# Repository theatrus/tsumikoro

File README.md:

# Tsumikoro

Open-source motor controller projects based on STM32G0 microcontrollers with ESP32 network bridge.

## Projects

| Project | Description | MCU | Flash/RAM | Framework | Status |
|---------|-------------|-----|-----------|-----------|--------|
| **tsumikoro-servo** | 6-channel servo + H-bridge motor controller | STM32G030F6P6TR | 32KB/8KB | STM32 LL | ✅ Functional (PR #9) |
| **tsumikoro-ministepper** | Mini stepper motor controller | STM32G071G8U6 | 64KB/36KB | STM32 HAL + FreeRTOS | 🚧 In Development |
| **tsumikoro-bridge** | WiFi/Network bridge (RS-485 bus) | ESP32/ESP32-S3 | 4MB+ | ESPHome | ✅ Functional (Merged) |
| **nucleo-g071rb** | Development firmware (bare-metal) | STM32G071RBT6 | 128KB/36KB | STM32 HAL | ✅ Development Tool (PR #11) |
| **nucleo-g071rb-freertos** | Development firmware (FreeRTOS) | STM32G071RBT6 | 128KB/36KB | STM32 HAL + FreeRTOS | ✅ Development Tool (PR #11) |

### Recent Updates

- **2025-11**: NUCLEO-G071RB development firmware with FreeRTOS integration (PR #11)
  - Bare-metal and FreeRTOS examples for bus protocol development
  - Stack monitoring and optimization (18KB heap, optimized task stacks)
  - Debug UART with statistics output and stack high-water marks
  - CI/CD integration for all firmware targets
- **2025-11**: Protocol improvements and bug fixes
  - Fixed escape sequence handling in packet END marker detection
  - Added comprehensive unit tests for bus handler (34 tests)
  - Integration tests for controller/peripheral communication
- **2025-11**: Multi-drop RS-485 bus protocol implemented with STM32 HAL
- **2025-11**: Servo controller: 6 PWM channels + H-bridge motor driver (89% Flash usage)
- **2025-11**: ESP32 bridge with Home Assistant integration
- **2025-11**: Unified build system with top-level Makefile and flash targets

## Repository Structure

```
tsumikoro/
├── firmware/                 # All firmware projects (C/C++, Apache 2.0)
│   ├── tsumikoro-ministepper/  # STM32G071 mini stepper controller (FreeRTOS)
│   ├── tsumikoro-servo/        # STM32G030 servo controller (bare-metal)
│   ├── tsumikoro-bridge/       # ESP32/ESP32-S3 network bridge (ESPHome)
│   │   ├── esphome/           # ESPHome configuration
│   │   └── components/        # Custom ESPHome components
│   ├── nucleo-g071rb/         # NUCLEO-G071RB development firmware (bare-metal)
│   ├── nucleo-g071rb-freertos/# NUCLEO-G071RB development firmware (FreeRTOS)
│   ├── common/                # Shared HAL and utilities (STM32, FreeRTOS)
│   └── shared/                # Shared protocol definitions and tests
│       └── tsumikoro_bus/    # Bus protocol library with unit tests
├── hardware/                 # PCB designs (coming soon, CERN-OHL-P v2)
├── mechanical/               # 3D models (coming soon, CERN-OHL-P v2)
└── LICENSE                  # Dual licensing information
```

## Quick Start

### Prerequisites

**For STM32 builds:**
- ARM GCC toolchain: `arm-none-eabi-gcc`
- CMake 3.20 or newer
- Make or Ninja build tool

**For ESP32 bridge:**
- Python 3.10+
- uv (Python package manager)

See [firmware/README.md](firmware/README.md) for detailed installation instructions.

### Build All Projects

```bash
# First-time setup
make setup

# Build everything
make build

# Or build individual projects
make build-servo       # STM32G030 servo controller
make build-ministepper # STM32G071 stepper controller
make build-bridge      # ESP32 network bridge
make build-nucleo      # NUCLEO-G071RB development boards

# Run protocol tests
make test

# Clean all builds
make clean

# View all available targets
make help
```

### Individual Project Builds

**Servo Controller (STM32G030):**
```bash
cd firmware
make servo-g030
make flash-servo-g030  # Flash using st-flash
# Output: build/servo-g030/tsumikoro-servo.bin
```

**Ministepper (STM32G071):**
```bash
cd firmware
make ministepper-g071
make flash-ministepper-g071
# Output: build/ministepper-g071/tsumikoro-ministepper.bin
```

**NUCLEO-G071RB Development Boards:**
```bash
cd firmware

# Bare-metal version
make nucleo-g071rb
make flash-nucleo-g071rb

# FreeRTOS version (with stack monitoring)
make nucleo-g071rb-freertos
make flash-nucleo-g071rb-freertos

# Reset target after flashing
make reset
```

**ESP32 Bridge:**
```bash
# First time setup
cd firmware/tsumikoro-bridge
make setup
cp esphome/secrets.yaml.example esphome/secrets.yaml
# Edit secrets.yaml with your WiFi credentials

# Build and upload
make build
make upload
```

## Key Features

### Tsumikoro Bus Protocol

Multi-drop RS-485 serial bus protocol for reliable motor controller communication:

- **Frame Format**: `[START][ID][CMD_HI][CMD_LO][LEN][DATA][CRC8][END]`
- **Packet Size**: 7-71 bytes (0-64 bytes data payload)
- **Addressing**: Controller (0x00) + up to 239 peripherals (0x01-0xEF)
- **Error Detection**: CRC8 checksum with frame markers
- **Command Ranges**:
  - `0x0000-0x0FFF`: Generic commands (ping, version, status)
  - `0x2000-0x2FFF`: Stepper motor commands
  - `0x3000-0x3FFF`: Servo motor commands
  - `0x4000-0x4FFF`: DC motor/H-bridge commands

### Servo Controller Features

**Hardware Capabilities:**
- 6 independent servo channels (50Hz PWM, 1-2ms pulse width)
- H-bridge motor driver (20kHz PWM speed control)
- 4 direction modes: FORWARD, REVERSE, BRAKE, COAST
- 0-180° servo position range (0.1° resolution)

**Control Features:**
- Smooth position transitions with configurable speed
- Per-channel calibration (500-2500µs pulse widths)
- Multi-servo synchronized movement
- Emergency stop function
- Hardware ID pins for device enumeration

**Resource Efficient:**
- Flash: 29.3KB / 32KB (89.42%)
- RAM: 2.2KB / 8KB (26.86%)
- Zero CPU overhead for PWM (hardware timers)

### ESP32 Bridge Features

- WiFi 802.11 b/g/n connectivity
- Home Assistant integration via ESPHome
- RS-485 bus communication with motor controllers
- Custom ESPHome components for Tsumikoro protocol
- OTA firmware updates

### FreeRTOS Integration

**Real-Time Operating System Support:**
- Preemptive multitasking with configurable priorities
- Dedicated RTOS threads for RX, TX, and bus handler
- Inter-task communication via queues and semaphores
- Stack overflow detection and monitoring
- Optimized heap and stack allocations (18KB heap, task-specific stacks)

**Development Tools:**
- Stack high-water mark monitoring via debug UART
- Runtime statistics (heap usage, IRQ counts, task states)
- Comprehensive unit tests for protocol and bus handler
- CI/CD integration for automated builds and testing

### Continuous Integration

**Automated Builds:**
- All firmware targets built automatically on push/PR
- Protocol unit tests run on every commit
- Artifacts retained for 30 days
- Multi-platform support (STM32 + ESP32)

**Build Matrix:**
- STM32 builds: servo-g030, ministepper-g071, nucleo-g071rb, nucleo-g071rb-freertos
- ESP32 builds: tsumikoro-bridge (ESPHome)
- Protocol tests: 151 assertions across CRC8, protocol, integration, and bus handler tests

## Hardware

### Motor Controllers (STM32)

**STM32G071G8U6** (Mini Stepper)
- 64KB Flash, 36KB RAM
- ARM Cortex-M0+ @ 64MHz
- UFQFPN28 package
- FreeRTOS support with optimized task stacks

**STM32G030F6P6TR** (Servo)
- 32KB Flash, 8KB RAM
- ARM Cortex-M0+ @ 64MHz
- TSSOP20 package
- Bare-metal for maximum efficiency

### Development Boards

**STM32 NUCLEO-G071RB**
- 128KB Flash, 36KB RAM
- ARM Cortex-M0+ @ 64MHz
- Arduino-compatible headers
- On-board ST-LINK debugger
- Available in both bare-metal and FreeRTOS firmware variants
- Ideal for bus protocol development and testing

### Network Bridge (ESP32)

**ESP32 / ESP32-S3**
- WiFi 802.11 b/g/n
- 4MB+ Flash recommended
- UART communication with motor controllers
- Home Assistant integration via ESPHome

## License

This project uses dual licensing:

- **Firmware/Software**: [Apache 2.0](firmware/LICENSE)
- **Hardware Designs**: CERN-OHL-P v2 (permissive open hardware)

See [LICENSE](LICENSE) for details.

## Contributing

Contributions are welcome! Please ensure:
- Firmware contributions follow the Apache 2.0 license
- Hardware contributions follow CERN-OHL-P v2
- Code follows the existing style
- All changes are tested

## Resources

### Documentation
- [STM32 Firmware Documentation](firmware/README.md)
- [ESP32 Bridge Documentation](firmware/tsumikoro-bridge/README.md)

### Hardware
- [STM32G0 Series](https://www.st.com/en/microcontrollers-microprocessors/stm32g0-series.html)
- [ESP32 Documentation](https://docs.espressif.com/projects/esp-idf/)
- [ESPHome](https://esphome.io/)

### Licenses
- [Apache 2.0 License](https://www.apache.org/licenses/LICENSE-2.0)
- [CERN-OHL-P v2](https://ohwr.org/cern_ohl_p_v2.txt)

### Tools
- [uv Python Package Manager](https://github.com/astral-sh/uv)

---

Copyright (c) 2025-2025 Yann Ramin

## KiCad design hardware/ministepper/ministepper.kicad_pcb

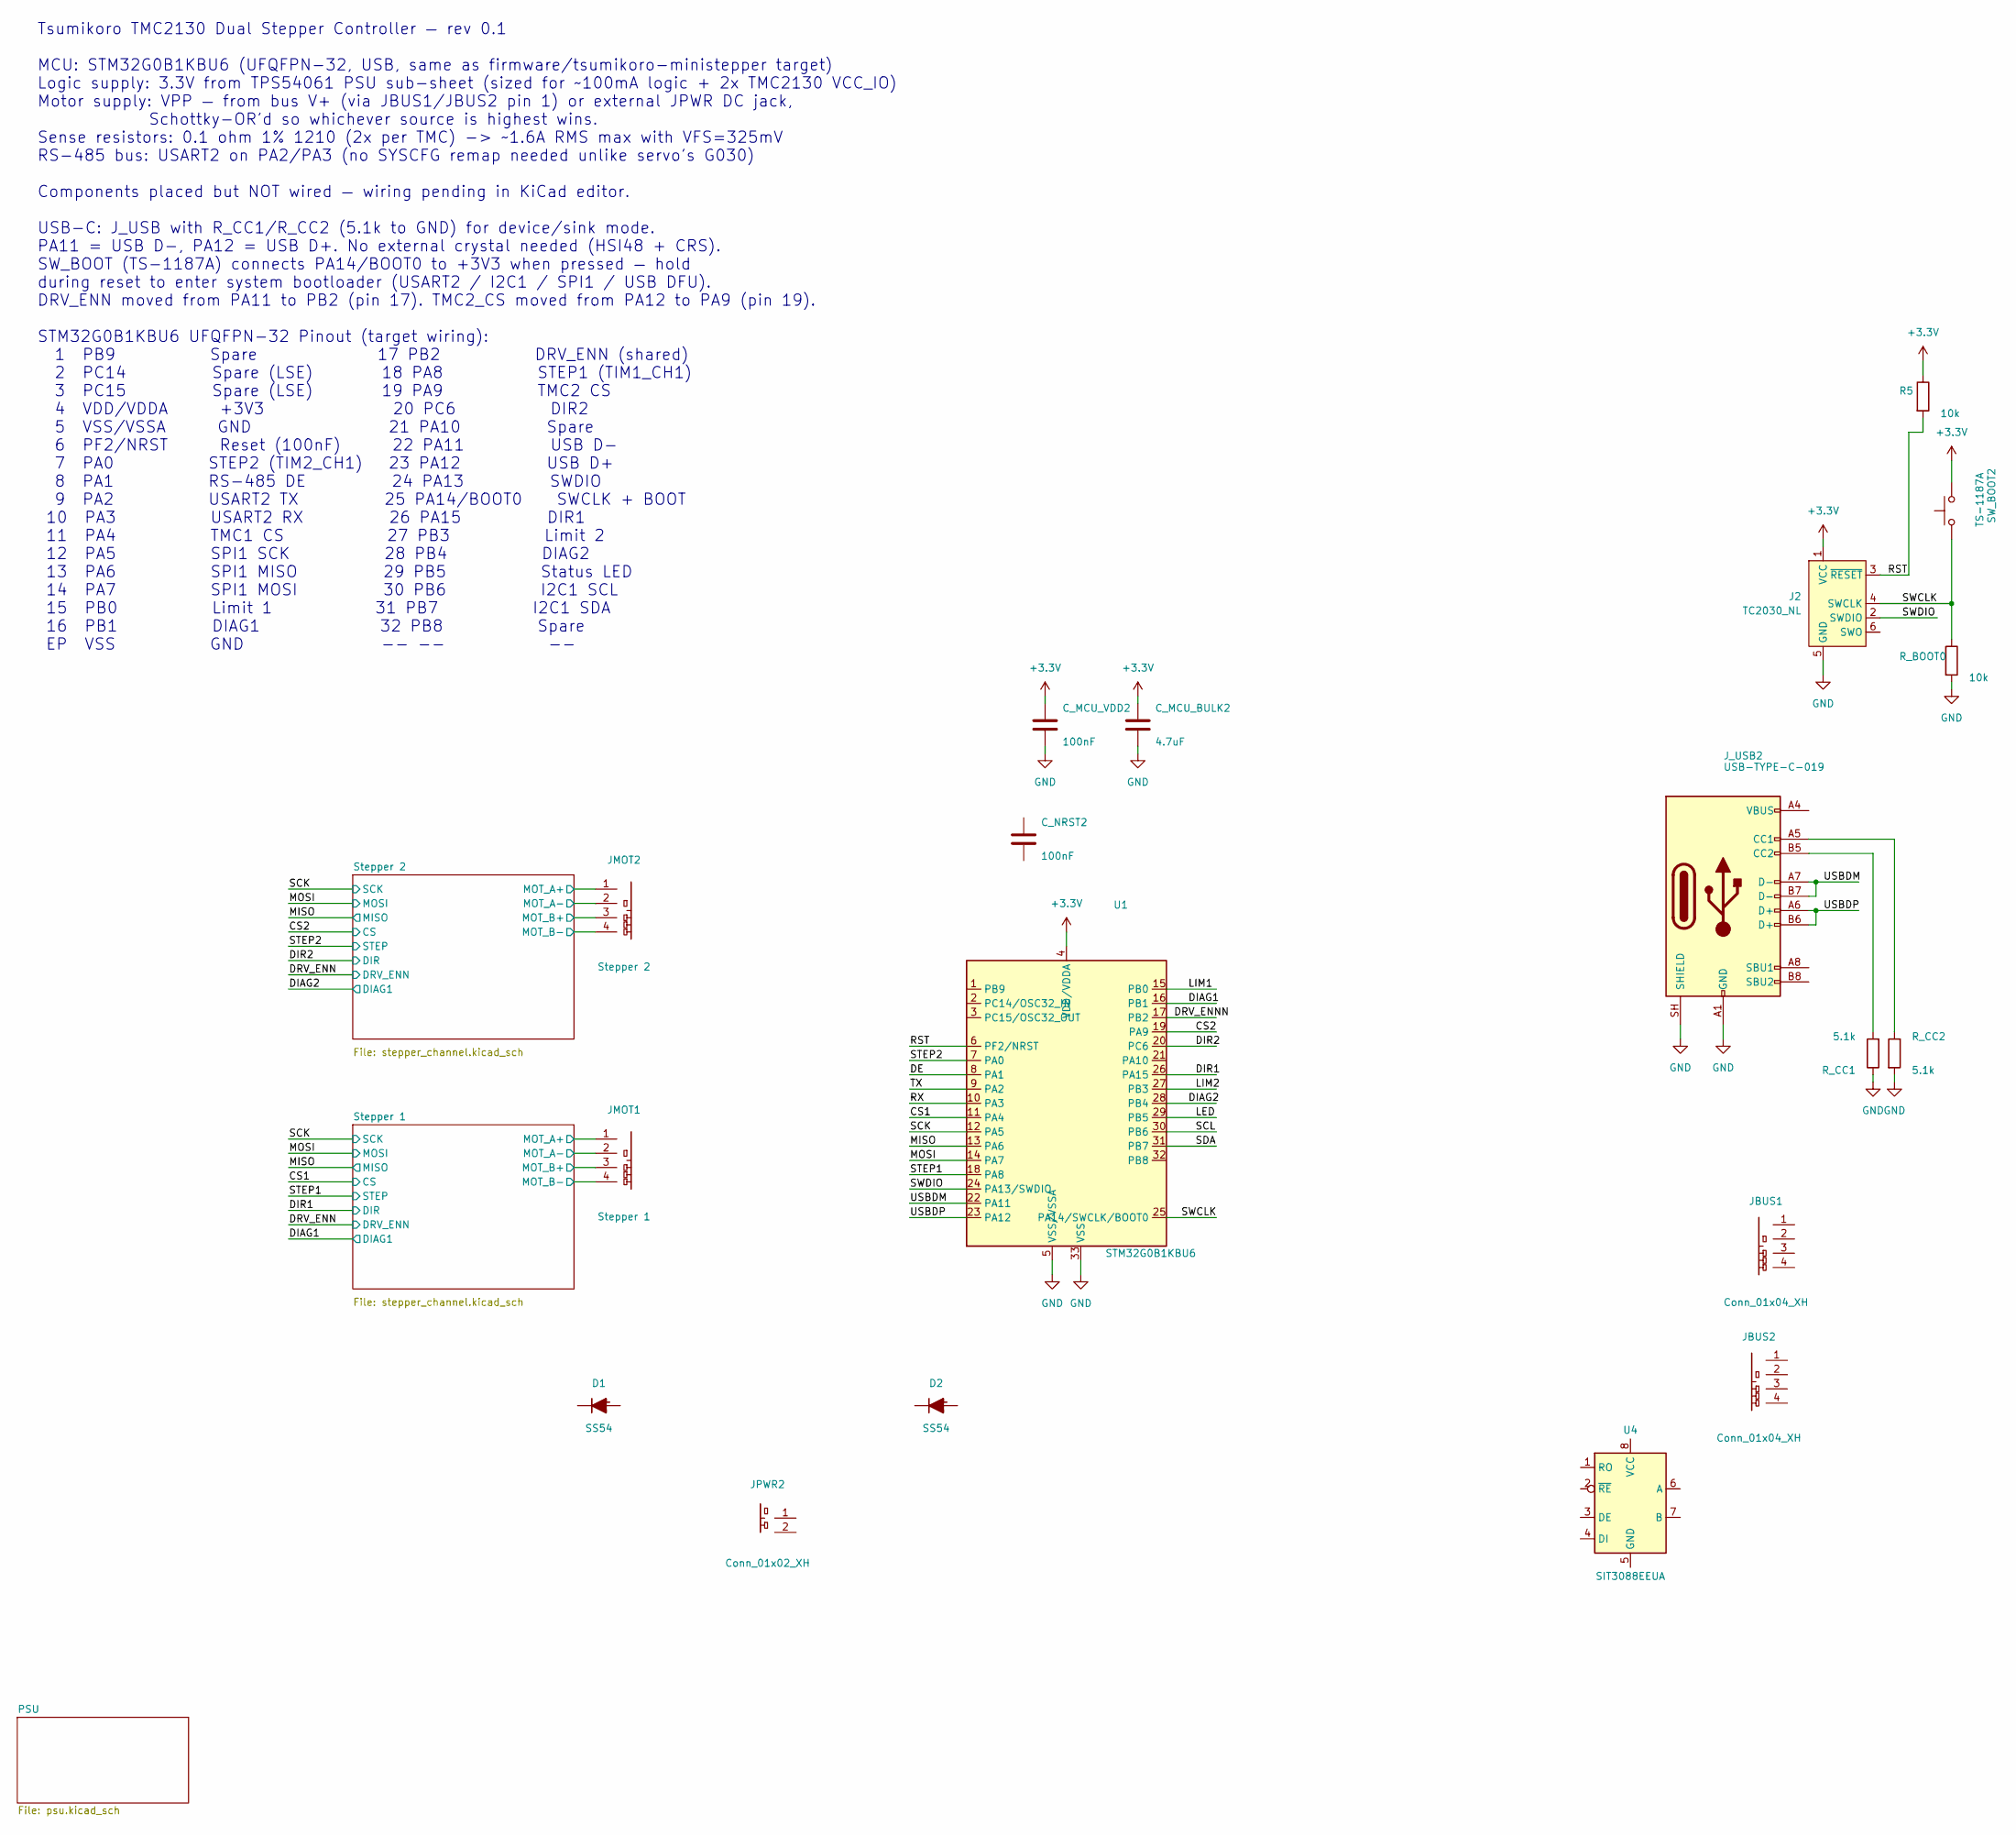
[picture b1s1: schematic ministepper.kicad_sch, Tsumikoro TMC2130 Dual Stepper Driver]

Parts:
C_MCU_BULK2: 4.7uF; C_0603_1608Metric; MPN CL10A475KO8NNNC; LCSC C19666
C_MCU_VDD2: 100nF; C_0402_1005Metric; MPN CL05B104KB54PNC; LCSC C307331
C_NRST2: 100nF; C_0402_1005Metric; MPN CL05B104KB54PNC; LCSC C307331
D1, D2: SS54; D_SMA; MPN SS54; LCSC C22452
J2: TC2030_NL; Tag-Connect_TC2030-IDC-NL_2x03_P1.27mm_Vertical
JBUS1, JBUS2: Conn_01x04_XH; JST_XH_S4B-XH-A_1x04_P2.50mm_Horizontal; MPN S4B-XH-A(LF)(SN); LCSC C157925
JMOT1: Stepper 1; JST_XH_B4B-XH-A_1x04_P2.50mm_Vertical; MPN B4B-XH-A-R(LF)(SN); LCSC C595709
JMOT2: Stepper 2; JST_XH_B4B-XH-A_1x04_P2.50mm_Vertical; MPN B4B-XH-A-R(LF)(SN); LCSC C595709
JPWR2: Conn_01x02_XH; JST_XH_S2B-XH-A_1x02_P2.50mm_Horizontal; MPN S2B-XH-A(LF)(SN); LCSC C157931
J_USB2: USB-TYPE-C-019; USB_C_Receptacle_GCT_USB4105-xx-A_16P_TopMnt_Horizontal; MPN USB-TYPE-C-019; LCSC C2927039
R5: 10k; R_0402_1005Metric; MPN 0402WGF1002TCE; LCSC C25744
R_BOOT0: 10k; R_0402_1005Metric; MPN 0402WGF1002TCE; LCSC C25744
R_CC1, R_CC2: 5.1k; R_0402_1005Metric; MPN 0402WGF5101TCE; LCSC C25905
SW_BOOT2: TS-1187A; SW_Push_1P1T_XKB_TS-1187A; MPN TS-1187A-B-A-B; LCSC C318884
U1: STM32G0B1KBU6; UFQFPN-32; MPN STM32G0B1KBU6; LCSC C5159549
U4: SIT3088EEUA; MSOP-8_3x3mm_P0.65mm; MPN SIT3088EEUA; LCSC C2922535

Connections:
+3.3V: C_MCU_BULK2.1, C_MCU_VDD2.1, J2.1 (VCC), R5.1, SW_BOOT2.2, U1.4 (VDD/VDDA); also elsewhere on the board
/CS1: U1.11 (PA4); also elsewhere on the board
/CS2: U1.19 (PA9); also elsewhere on the board
/DE: U1.8 (PA1)
/DIAG1: U1.16 (PB1); also elsewhere on the board
/DIAG2: U1.28 (PB4); also elsewhere on the board
/DIR1: U1.26 (PA15); also elsewhere on the board
/DIR2: U1.20 (PC6); also elsewhere on the board
/DRV_ENNN: U1.17 (PB2)
/LED: U1.29 (PB5)
/LIM1: U1.15 (PB0)
/LIM2: U1.27 (PB3)
/MISO: U1.13 (PA6); also elsewhere on the board
/MOSI: U1.14 (PA7); also elsewhere on the board
/RST: J2.3 (~RESET), R5.2, U1.6 (PF2/NRST)
/RX: U1.10 (PA3)
/SCK: U1.12 (PA5); also elsewhere on the board
/SCL: U1.30 (PB6)
/SDA: U1.31 (PB7)
/STEP1: U1.18 (PA8); also elsewhere on the board
/STEP2: U1.7 (PA0); also elsewhere on the board
/SWCLK: J2.4 (SWCLK), R_BOOT0.1, SW_BOOT2.1, U1.25 (PA14/SWCLK/BOOT0)
/SWDIO: J2.2 (SWDIO), U1.24 (PA13/SWDIO)
/Stepper 1/MOT_A+: JMOT1.1; also elsewhere on the board
/Stepper 1/MOT_A-: JMOT1.2; also elsewhere on the board
/Stepper 1/MOT_B+: JMOT1.3; also elsewhere on the board
/Stepper 1/MOT_B-: JMOT1.4; also elsewhere on the board
/Stepper 2/MOT_A+: JMOT2.1; also elsewhere on the board
/Stepper 2/MOT_A-: JMOT2.2; also elsewhere on the board
/Stepper 2/MOT_B+: JMOT2.3; also elsewhere on the board
/Stepper 2/MOT_B-: JMOT2.4; also elsewhere on the board
/TX: U1.9 (PA2)
/USBDM: J_USB2.A7 (D-), J_USB2.B7 (D-), U1.22 (PA11)
/USBDP: J_USB2.A6 (D+), J_USB2.B6 (D+), U1.23 (PA12)
GND: C_MCU_BULK2.2, C_MCU_VDD2.2, J2.5 (GND), J_USB2.A1 (GND), J_USB2.A12 (GND), J_USB2.B1 (GND), J_USB2.B12 (GND), J_USB2.SH (SHIELD), R_BOOT0.2, R_CC1.1, R_CC2.2, U1.5 (VSS/VSSA), U1.33 (VSS); also elsewhere on the board
unnamed: J_USB2.A5 (CC1), R_CC2.1
unnamed: J_USB2.B5 (CC2), R_CC1.2
unnamed: J_USB2.A4 (VBUS), J_USB2.A9 (VBUS), J_USB2.B4 (VBUS), J_USB2.B9 (VBUS)

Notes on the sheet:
Tsumikoro TMC2130 Dual Stepper Controller — rev 0.1 MCU: STM32G0B1KBU6 (UFQFPN-32, USB, same as firmware/tsumikoro-ministepper target) Logic supply: 3.3V from TPS54061 PSU sub-sheet (sized for ~100mA logic + 2x TMC2130 VCC_IO) Motor supply: VPP — from bus V+ (via JBUS1/JBUS2 pin 1) or external JPWR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

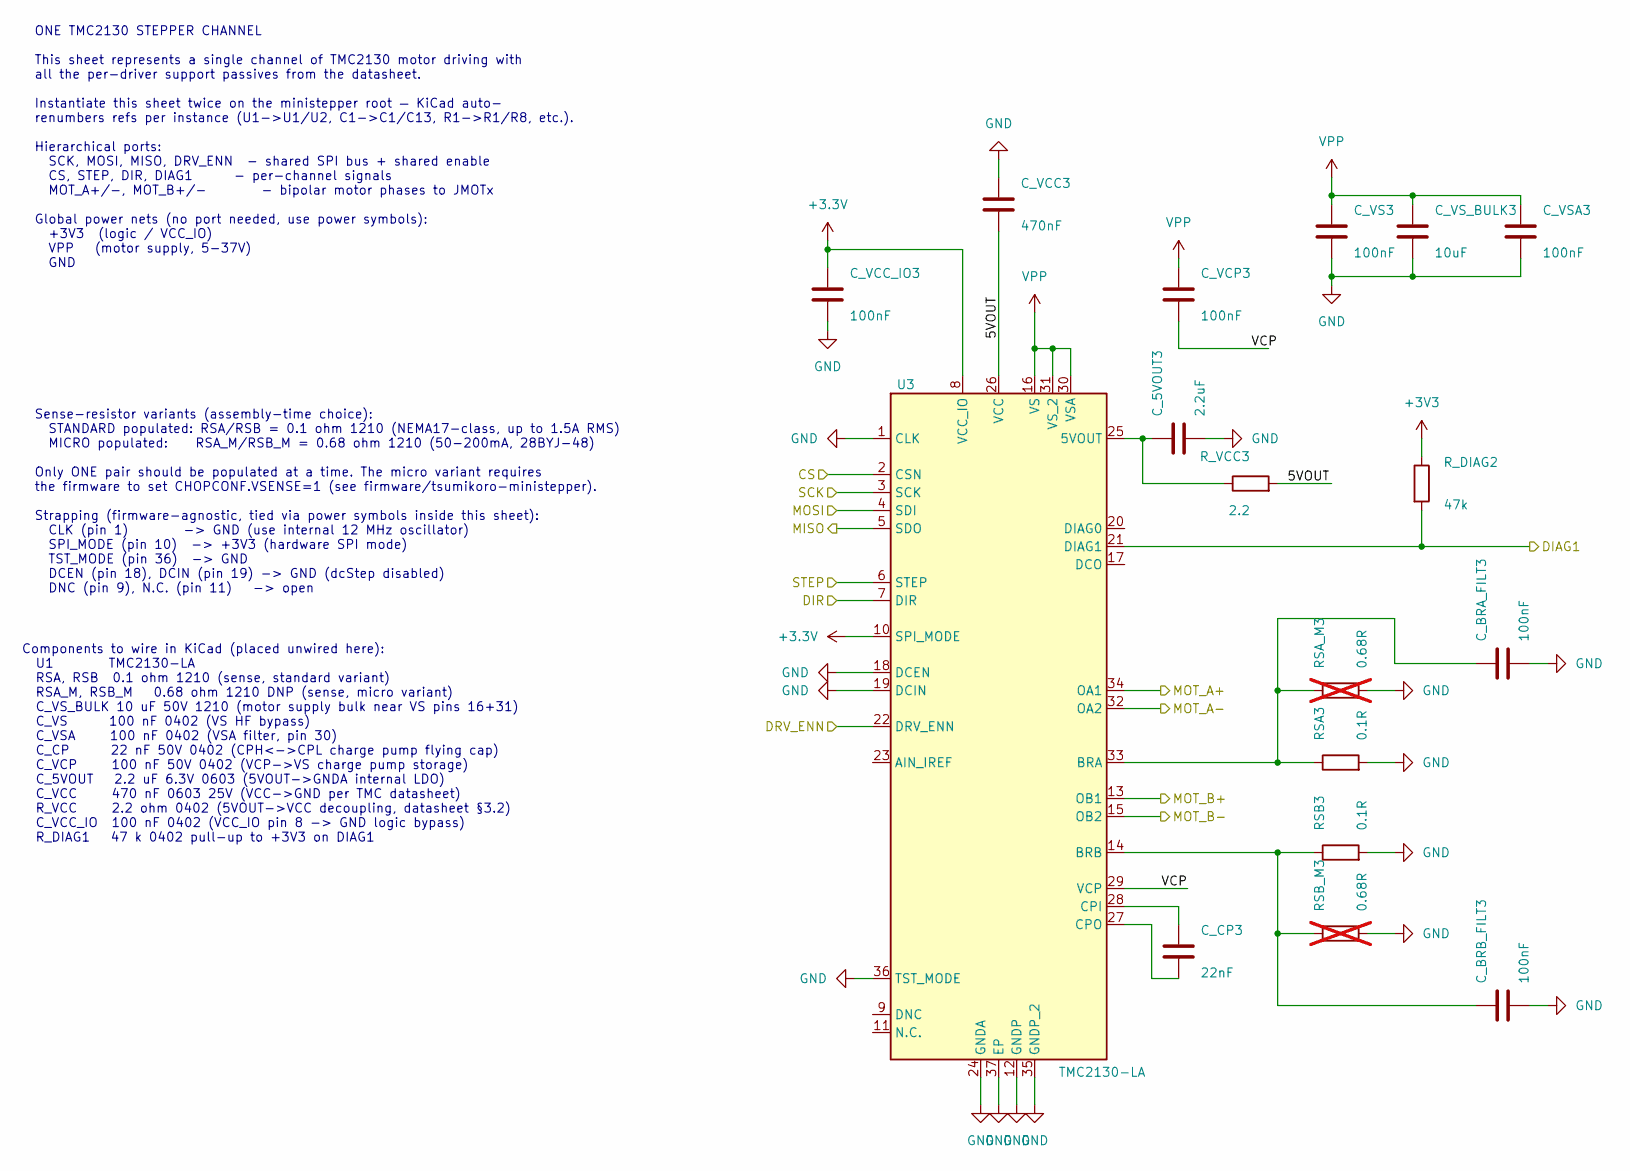
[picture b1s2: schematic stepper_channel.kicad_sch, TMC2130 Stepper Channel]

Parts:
C_5VOUT3: 2.2uF; C_0603_1608Metric; MPN TCC0603X5R226M6R3CT; LCSC C380323
C_BRA_FILT3: 100nF; C_0402_1005Metric; MPN CL05B104KB54PNC; LCSC C307331
C_BRB_FILT3: 100nF; C_0402_1005Metric; MPN CL05B104KB54PNC; LCSC C307331
C_CP3: 22nF; C_0402_1005Metric; MPN 0402B223K500NT; LCSC C1532
C_VCC3: 470nF; C_0603_1608Metric; MPN CL10B474KA8NNNC; LCSC C1623
C_VCC_IO3: 100nF; C_0402_1005Metric; MPN CL05B104KB54PNC; LCSC C307331
C_VCP3: 100nF; C_0402_1005Metric; MPN CL05B104KB54PNC; LCSC C307331
C_VS3: 100nF; C_0402_1005Metric; MPN CL05B104KB54PNC; LCSC C307331
C_VSA3: 100nF; C_0402_1005Metric; MPN CL05B104KB54PNC; LCSC C307331
C_VS_BULK3: 10uF; C_1210_3225Metric; MPN CS3225X7R106K500NRL; LCSC C2918502
RSA3: 0.1R; R_1210_3225Metric; MPN FRL1210FR100TS; LCSC C2974119
RSA_M3: 0.68R; R_1210_3225Metric; MPN FRC1210F68R0TS; LCSC C3000593; not fitted
RSB3: 0.1R; R_1210_3225Metric; MPN FRL1210FR100TS; LCSC C2974119
RSB_M3: 0.68R; R_1210_3225Metric; MPN FRC1210F68R0TS; LCSC C3000593; not fitted
R_DIAG2: 47k; R_0402_1005Metric; MPN RC0402FR-0747KL; LCSC C93943
R_VCC3: 2.2; R_0402_1005Metric; MPN RC-02U2R20FT; LCSC C321161
U3: TMC2130-LA; QFN-36-1EP_5x6mm_P0.5mm_EP3.6x4.6mm; MPN TMC2130-LA-T; LCSC C915795

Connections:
+3.3V: C_VCC_IO3.1, U3.8 (VCC_IO), U3.10 (SPI_MODE); also elsewhere on the board
+3V3: R_DIAG2.1; also elsewhere on the board
/CS2: U3.2 (CSN); also elsewhere on the board
/DIAG2: R_DIAG2.2, U3.21 (DIAG1); also elsewhere on the board
/DIR2: U3.7 (DIR); also elsewhere on the board
/DRV_ENN: U3.22 (DRV_ENN); also elsewhere on the board
/MISO: U3.5 (SDO); also elsewhere on the board
/MOSI: U3.4 (SDI); also elsewhere on the board
/SCK: U3.3 (SCK); also elsewhere on the board
/STEP2: U3.6 (STEP); also elsewhere on the board
/Stepper 2/5VOUT: C_VCC3.2, R_VCC3.2, U3.26 (VCC)
/Stepper 2/MOT_A+: U3.34 (OA1); also elsewhere on the board
/Stepper 2/MOT_A-: U3.32 (OA2); also elsewhere on the board
/Stepper 2/MOT_B+: U3.13 (OB1); also elsewhere on the board
/Stepper 2/MOT_B-: U3.15 (OB2); also elsewhere on the board
/Stepper 2/VCP: C_VCP3.2, U3.29 (VCP)
GND: C_5VOUT3.2, C_BRA_FILT3.2, C_BRB_FILT3.2, C_VCC3.1, C_VCC_IO3.2, C_VS3.2, C_VSA3.2, C_VS_BULK3.2, RSA3.2, RSA_M3.2, RSB3.2, RSB_M3.2, U3.1 (CLK), U3.12 (GNDP), U3.18 (DCEN), U3.19 (DCIN), U3.24 (GNDA), U3.35 (GNDP_2), U3.36 (TST_MODE), U3.37 (EP); also elsewhere on the board
unnamed: C_5VOUT3.1, R_VCC3.1, U3.25 (5VOUT)
unnamed: C_BRA_FILT3.1, RSA3.1, U3.33 (BRA)
unnamed: C_BRB_FILT3.1, RSB3.1, U3.14 (BRB)
unnamed: C_CP3.1, U3.28 (CPI)
unnamed: C_CP3.2, U3.27 (CPO)
VPP: C_VCP3.1, C_VS3.1, C_VSA3.1, C_VS_BULK3.1, U3.16 (VS), U3.30 (VSA), U3.31 (VS_2); also elsewhere on the board

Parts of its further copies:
C_5VOUT2: 2.2uF; C_0603_1608Metric; MPN TCC0603X5R226M6R3CT; LCSC C380323
C_BRA_FILT2: 100nF; C_0402_1005Metric; MPN CL05B104KB54PNC; LCSC C307331
C_BRB_FILT2: 100nF; C_0402_1005Metric; MPN CL05B104KB54PNC; LCSC C307331
C_CP2: 22nF; C_0402_1005Metric; MPN 0402B223K500NT; LCSC C1532
C_VCC2: 470nF; C_0603_1608Metric; MPN CL10B474KA8NNNC; LCSC C1623
C_VCC_IO2: 100nF; C_0402_1005Metric; MPN CL05B104KB54PNC; LCSC C307331
C_VCP2: 100nF; C_0402_1005Metric; MPN CL05B104KB54PNC; LCSC C307331
C_VS2: 100nF; C_0402_1005Metric; MPN CL05B104KB54PNC; LCSC C307331
C_VSA2: 100nF; C_0402_1005Metric; MPN CL05B104KB54PNC; LCSC C307331
C_VS_BULK2: 10uF; C_1210_3225Metric; MPN CS3225X7R106K500NRL; LCSC C2918502
RSA2: 0.1R; R_1210_3225Metric; MPN FRL1210FR100TS; LCSC C2974119
RSB2: 0.1R; R_1210_3225Metric; MPN FRL1210FR100TS; LCSC C2974119
R_DIAG1: 47k; R_0402_1005Metric; MPN RC0402FR-0747KL; LCSC C93943
R_VCC2: 2.2; R_0402_1005Metric; MPN RC-02U2R20FT; LCSC C321161
U2: TMC2130-LA; QFN-36-1EP_5x6mm_P0.5mm_EP3.6x4.6mm; MPN TMC2130-LA-T; LCSC C915795

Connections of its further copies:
+3.3V: C_VCC_IO2.1, U2.8 (VCC_IO), U2.10 (SPI_MODE); also elsewhere on the board
+3V3: R_DIAG1.1; also elsewhere on the board
/CS1: U2.2 (CSN); also elsewhere on the board
/DIAG1: R_DIAG1.2, U2.21 (DIAG1); also elsewhere on the board
/DIR1: U2.7 (DIR); also elsewhere on the board
/DRV_ENN: U2.22 (DRV_ENN); also elsewhere on the board
/MISO: U2.5 (SDO); also elsewhere on the board
/MOSI: U2.4 (SDI); also elsewhere on the board
/SCK: U2.3 (SCK); also elsewhere on the board
/STEP1: U2.6 (STEP); also elsewhere on the board
/Stepper 1/5VOUT: C_VCC2.2, R_VCC2.2, U2.26 (VCC)
/Stepper 1/MOT_A+: U2.34 (OA1); also elsewhere on the board
/Stepper 1/MOT_A-: U2.32 (OA2); also elsewhere on the board
/Stepper 1/MOT_B+: U2.13 (OB1); also elsewhere on the board
/Stepper 1/MOT_B-: U2.15 (OB2); also elsewhere on the board
/Stepper 1/VCP: C_VCP2.2, U2.29 (VCP)
GND: C_5VOUT2.2, C_BRA_FILT2.2, C_BRB_FILT2.2, C_VCC2.1, C_VCC_IO2.2, C_VS2.2, C_VSA2.2, C_VS_BULK2.2, RSA2.2, RSB2.2, U2.1 (CLK), U2.12 (GNDP), U2.18 (DCEN), U2.19 (DCIN), U2.24 (GNDA), U2.35 (GNDP_2), U2.36 (TST_MODE), U2.37 (EP); also elsewhere on the board
unnamed: C_5VOUT2.1, R_VCC2.1, U2.25 (5VOUT)
unnamed: C_BRA_FILT2.1, RSA2.1, U2.33 (BRA)
unnamed: C_BRB_FILT2.1, RSB2.1, U2.14 (BRB)
unnamed: C_CP2.1, U2.28 (CPI)
unnamed: C_CP2.2, U2.27 (CPO)
VPP: C_VCP2.1, C_VS2.1, C_VSA2.1, C_VS_BULK2.1, U2.16 (VS), U2.30 (VSA), U2.31 (VS_2); also elsewhere on the board

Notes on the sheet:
Components to wire in KiCad (placed unwired here): U1 TMC2130-LA RSA, RSB 0.1 ohm 1210 (sense, standard variant) RSA_M, RSB_M 0.68 ohm 1210 DNP (sense, micro variant) C_VS_BULK 10 uF 50V 1210 (motor supply bulk near VS pins 16+31) C_VS 100 nF 0402 (VS HF bypass) C_VSA 100 nF 0402 (VSA filter, pin 3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
ONE TMC2130 STEPPER CHANNEL This sheet represents a single channel of TMC2130 motor driving with all the per-driver support passives from the datasheet. Instantiate this sheet twice on the ministepper root — KiCad auto- renumbers refs per instance (U1->U1/U2, C1->C1/C13, R1->R1/R8, etc.). Hierarchi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
Sense-resistor variants (assembly-time choice): STANDARD populated: RSA/RSB = 0.1 ohm 1210 (NEMA17-class, up to 1.5A RMS) MICRO populated: RSA_M/RSB_M = 0.68 ohm 1210 (50-200mA, 28BYJ-48) Only ONE pair should be populated at a time. The micro variant requires the firmware to set CHOPCONF.VSENSE=1 (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

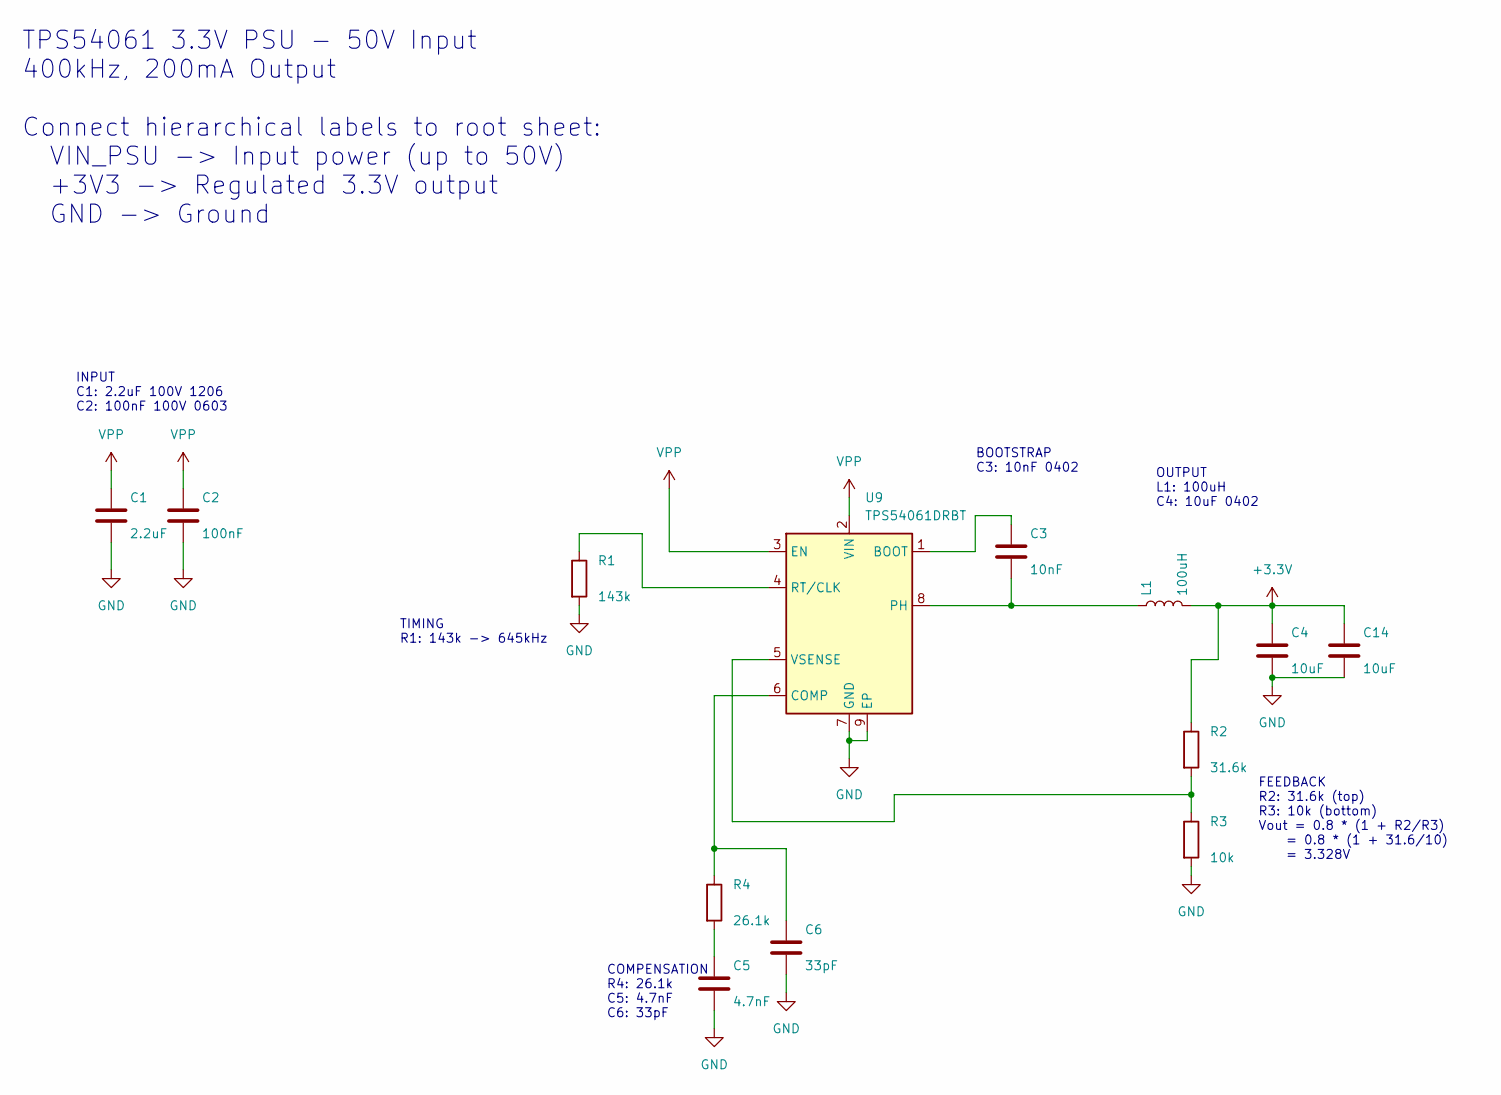
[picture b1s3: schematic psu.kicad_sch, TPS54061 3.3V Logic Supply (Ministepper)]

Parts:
C1: 2.2uF; C_1206_3216Metric; MPN CL31B225KCHSNNE; LCSC C170101
C2: 100nF; C_0603_1608Metric; MPN CC0603KRX7R0BB104; LCSC C113803
C3: 10nF; C_0402_1005Metric; MPN CL05B103KB5NNNC; LCSC C15195
C4, C14: 10uF; C_0402_1005Metric; MPN CL05A106MP5NUNC; LCSC C315248
C5: 4.7nF; C_0402_1005Metric; MPN 0402B472K500NT; LCSC C1538
C6: 33pF; C_0402_1005Metric; MPN CC0402JRNPO9BN330; LCSC C107005
L1: 100uH; L_Sunlord_SWPA4018S; MPN LVS404018-101M-N; LCSC C142135
R1: 143k; R_0402_1005Metric; MPN 0402WGF1433TCE; LCSC C82292
R2: 31.6k; R_0402_1005Metric; MPN 0402WGF3163TCE; LCSC C25777
R3: 10k; R_0402_1005Metric; MPN 0402WGF1002TCE; LCSC C25744
R4: 26.1k; R_0402_1005Metric; MPN 0402WGF2613TCE; LCSC C27003
U9: TPS54061DRBT; Texas_S-PVSON-N8; MPN TPS54061DRBT; LCSC C2070655

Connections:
+3.3V: C4.1, C14.1, L1.2, R2.1; also elsewhere on the board
GND: C1.2, C2.2, C4.2, C5.2, C6.2, C14.2, R1.2, R3.2, U9.7 (GND), U9.9 (EP); also elsewhere on the board
unnamed: C5.1, R4.2
unnamed: C3.1, U9.1 (BOOT)
unnamed: C6.1, R4.1, U9.6 (COMP)
unnamed: C3.2, L1.1, U9.8 (PH)
unnamed: R1.1, U9.4 (RT/CLK)
unnamed: R2.2, R3.1, U9.5 (VSENSE)
VPP: C1.1, C2.1, U9.2 (VIN), U9.3 (EN); also elsewhere on the board

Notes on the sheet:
TPS54061 3.3V PSU - 50V Input 400kHz, 200mA Output Connect hierarchical labels to root sheet: VIN_PSU -> Input power (up to 50V) +3V3 -> Regulated 3.3V output GND -> Ground
COMPENSATION R4: 26.1k C5: 4.7nF C6: 33pF
OUTPUT L1: 100uH C4: 10uF 0402
TIMING R1: 143k -> 645kHz
INPUT C1: 2.2uF 100V 1206 C2: 100nF 100V 0603
FEEDBACK R2: 31.6k (top) R3: 10k (bottom) Vout = 0.8 * (1 + R2/R3) = 0.8 * (1 + 31.6/10) = 3.328V
BOOTSTRAP C3: 10nF 0402

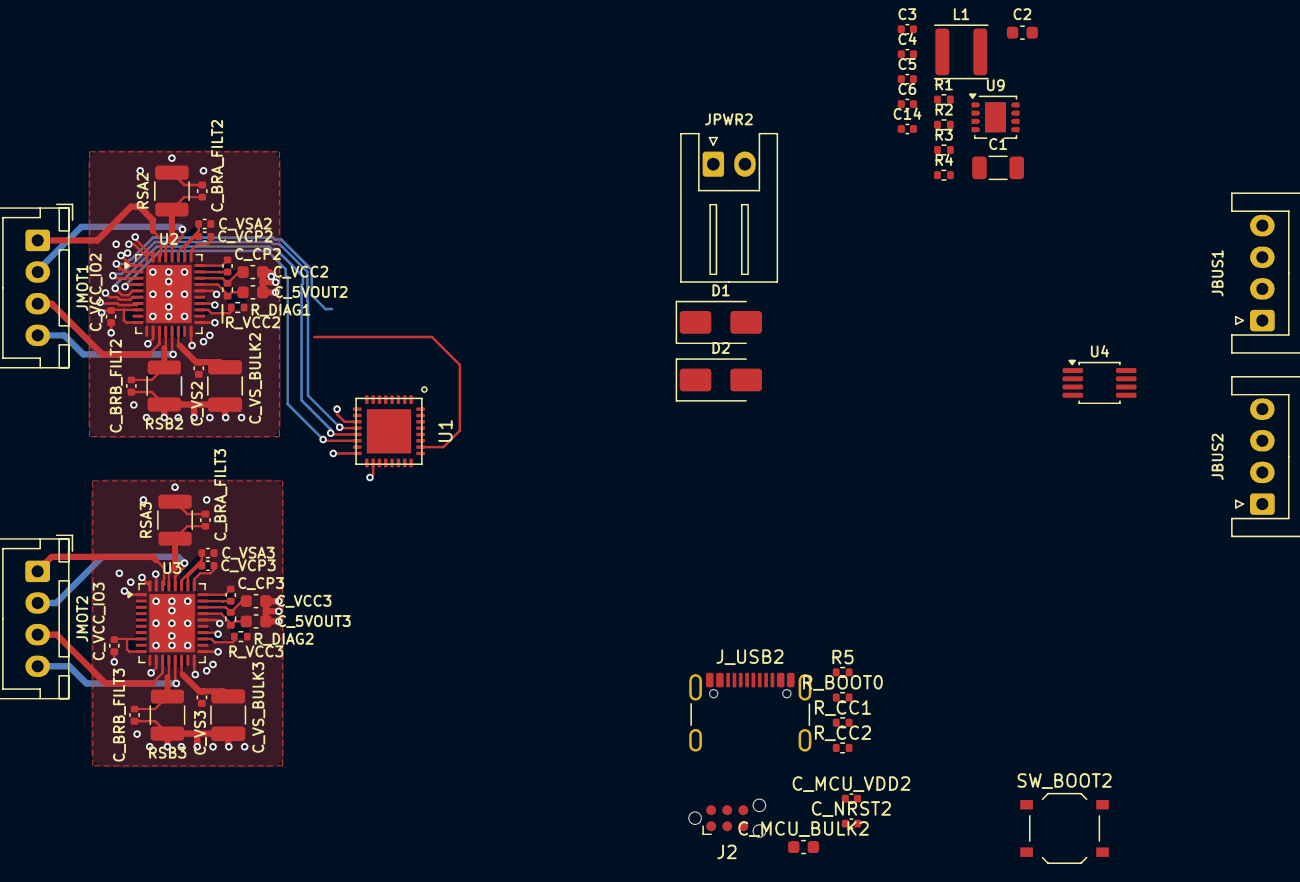
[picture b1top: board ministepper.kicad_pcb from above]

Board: 4 copper layers, 62 parts (0 on the bottom side), 52 nets.

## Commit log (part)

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2025-11-03 Move
2025-11-03 Add tsumikoro-bridge Makefile for CI builds
    - Add Makefile with recreate-venv target for GitHub Actions
    - Provides uv-based build system with proper venv setup
    - Required for ESP32 bridge CI workflow
2025-11-03 ci(deps): bump astral-sh/setup-uv from 6 to 7
    Bumps [astral-sh/setup-uv](https://github.com/astral-sh/setup-uv) from 6 to 7.
    - [Release notes](https://github.com/astral-sh/setup-uv/releases)
    - [Commits](https://github.com/astral-sh/setup-uv/compare/v6...v7)
    ---
    updated-dependencies:
    - dependency-name: astral-sh/setup-uv
2025-11-08 Initial plan
2025-11-24 ci(deps): bump actions/checkout from 5 to 6
    Bumps [actions/checkout](https://github.com/actions/checkout) from 5 to 6.
    - [Release notes](https://github.com/actions/checkout/releases)
    - [Changelog](https://github.com/actions/checkout/blob/main/CHANGELOG.md)
    - [Commits](https://github.com/actions/checkout/compare/v5...v6)
    ---
    updated-dependencies:
2025-12-08 deps(deps): bump firmware/common/STM32CubeG0 from `b03b3c8` to `1026dee`
    Bumps [firmware/common/STM32CubeG0](https://github.com/STMicroelectronics/STM32CubeG0) from `b03b3c8` to `1026dee`.
    - [Commits](https://github.com/STMicroelectronics/STM32CubeG0/compare/b03b3c8ffc326213ef98da8811f3f8173059e127...1026dee7c0d2dc6b7386c92090495c3d1feae0f4)
    ---
    updated-dependencies:
    - dependency-name: firmware/common/STM32CubeG0
    dependency-version: 1026dee7c0d2dc6b7386c92090495c3d1feae0f4
2025-12-15 deps(deps): bump esphome
    Bumps the esphome group in /firmware/tsumikoro-bridge with 1 update: [esphome](https://github.com/esphome/esphome).
    Updates `esphome` from 2025.11.4 to 2025.11.5
    - [Release notes](https://github.com/esphome/esphome/releases)
    - [Commits](https://github.com/esphome/esphome/compare/2025.11.4...2025.11.5)
    ---
    updated-dependencies:
2025-12-15 ci(deps): bump actions/upload-artifact from 5 to 6 (#22)
    Bumps [actions/upload-artifact](https://github.com/actions/upload-artifact) from 5 to 6.
    - [Release notes](https://github.com/actions/upload-artifact/releases)
    - [Commits](https://github.com/actions/upload-artifact/compare/v5...v6)
    ---
    updated-dependencies:
    - dependency-name: actions/upload-artifact
2025-12-29 deps(deps): bump firmware/common/STM32CubeG0 from `1026dee` to `24d1325` (#24)
    Bumps [firmware/common/STM32CubeG0](https://github.com/STMicroelectronics/STM32CubeG0) from `1026dee` to `24d1325`.
    - [Commits](https://github.com/STMicroelectronics/STM32CubeG0/compare/1026dee7c0d2dc6b7386c92090495c3d1feae0f4...24d13255ffa4eca73d133561a3df72f7df90d302)
    ---
    updated-dependencies:
    - dependency-name: firmware/common/STM32CubeG0
    dependency-version: 24d13255ffa4eca73d133561a3df72f7df90d302
2026-01-05 deps(deps): bump esphome (#26)
    Bumps the esphome group in /firmware/tsumikoro-bridge with 1 update: [esphome](https://github.com/esphome/esphome).
    Updates `esphome` from 2025.12.2 to 2025.12.4
    - [Release notes](https://github.com/esphome/esphome/releases)
    - [Commits](https://github.com/esphome/esphome/compare/2025.12.2...2025.12.4)
    ---
    updated-dependencies:
2026-01-19 deps(deps): bump esphome
    Bumps the esphome group in /firmware/tsumikoro-bridge with 1 update: [esphome](https://github.com/esphome/esphome).
    Updates `esphome` from 2025.12.5 to 2025.12.7
    - [Release notes](https://github.com/esphome/esphome/releases)
    - [Commits](https://github.com/esphome/esphome/compare/2025.12.5...2025.12.7)
    ---
    updated-dependencies:
2026-02-02 deps(deps): bump firmware/common/STM32CubeG0 from `24d1325` to `c80de4e`
    Bumps [firmware/common/STM32CubeG0](https://github.com/STMicroelectronics/STM32CubeG0) from `24d1325` to `c80de4e`.
    - [Commits](https://github.com/STMicroelectronics/STM32CubeG0/compare/24d13255ffa4eca73d133561a3df72f7df90d302...c80de4e0d658e27514f90eaf3c8ce8d00c95cca5)
    ---
    updated-dependencies:
    - dependency-name: firmware/common/STM32CubeG0
    dependency-version: c80de4e0d658e27514f90eaf3c8ce8d00c95cca5
2026-02-02 deps(deps): bump esphome (#31)
    Bumps the esphome group in /firmware/tsumikoro-bridge with 1 update: [esphome](https://github.com/esphome/esphome).
    Updates `esphome` from 2026.1.2 to 2026.1.3
    - [Release notes](https://github.com/esphome/esphome/releases)
    - [Commits](https://github.com/esphome/esphome/compare/2026.1.2...2026.1.3)
    ---
    updated-dependencies:
2026-02-16 deps(deps): bump esphome (#33)
    Bumps the esphome group in /firmware/tsumikoro-bridge with 1 update: [esphome](https://github.com/esphome/esphome).
    Updates `esphome` from 2026.1.4 to 2026.1.5
    - [Release notes](https://github.com/esphome/esphome/releases)
    - [Commits](https://github.com/esphome/esphome/compare/2026.1.4...2026.1.5)
    ---
    updated-dependencies:
2026-03-02 ci(deps): bump actions/upload-artifact from 6 to 7
    Bumps [actions/upload-artifact](https://github.com/actions/upload-artifact) from 6 to 7.
    - [Release notes](https://github.com/actions/upload-artifact/releases)
    - [Commits](https://github.com/actions/upload-artifact/compare/v6...v7)
    ---
    updated-dependencies:
    - dependency-name: actions/upload-artifact
2026-03-09 deps(deps): bump firmware/common/STM32CubeG0 from `c80de4e` to `bb9ba2a`
    Bumps [firmware/common/STM32CubeG0](https://github.com/STMicroelectronics/STM32CubeG0) from `c80de4e` to `bb9ba2a`.
    - [Commits](https://github.com/STMicroelectronics/STM32CubeG0/compare/c80de4e0d658e27514f90eaf3c8ce8d00c95cca5...bb9ba2a8e76638c497b77be70a34763573ceaffd)
    ---
    updated-dependencies:
    - dependency-name: firmware/common/STM32CubeG0
    dependency-version: bb9ba2a8e76638c497b77be70a34763573ceaffd
2026-03-09 deps(deps): bump esphome (#38)
    Bumps the esphome group in /firmware/tsumikoro-bridge with 1 update: [esphome](https://github.com/esphome/esphome).
    Updates `esphome` from 2026.2.2 to 2026.2.4
    - [Release notes](https://github.com/esphome/esphome/releases)
    - [Commits](https://github.com/esphome/esphome/compare/2026.2.2...2026.2.4)
    ---
    updated-dependencies:
2026-03-23 deps(deps): bump esphome (#40)
    Bumps the esphome group in /firmware/tsumikoro-bridge with 1 update: [esphome](https://github.com/esphome/esphome).
    Updates `esphome` from 2026.2.4 to 2026.3.1
    - [Release notes](https://github.com/esphome/esphome/releases)
    - [Commits](https://github.com/esphome/esphome/compare/2026.2.4...2026.3.1)
    ---
    updated-dependencies:
2026-04-13 gitignore
2026-04-13 deps(deps-dev): update ruff requirement
    Updates the requirements on [ruff](https://github.com/astral-sh/ruff) to permit the latest version.
    Updates `ruff` to 0.15.10
    - [Release notes](https://github.com/astral-sh/ruff/releases)
    - [Changelog](https://github.com/astral-sh/ruff/blob/main/CHANGELOG.md)
    - [Commits](https://github.com/astral-sh/ruff/compare/0.8.0...0.15.10)
    ---
2026-04-14 hardware: add JLCPCB fab/assembly package generator
    - hardware/scripts/jlcpcb-package.sh: reusable script producing gerbers
    (auto-detects 2 vs 4 layer), merged Excellon drill, JLCPCB-format BOM,
    and JLCPCB-format CPL (Designator, Mid X/Y, Rotation, Layer). Output
    zipped ready for upload to cart.jlcpcb.com/quote.
    - hardware/Makefile: add `make jlc` and `make jlc-servo` targets calling
    the script, plus `make clean-jlc` to remove generated packages.
2026-04-14 hardware: track JLCPCB output directory (but not the zip)
    Version the generated gerbers/drill/BOM/CPL so each commit captures the
    exact fab/assembly artifacts. The zip is redundant (one `zip -r` away
    from the tracked files) so it stays in .gitignore.
2026-04-14 hardware: bridge adds DC barrel jacks with reverse-polarity protection
    - JDC1, JDC2: JLCPCB C2880546 DC-005K-5A-2.0 barrel jacks (2.0 mm center
    pin, 5.5 mm OD), one per bus connector. Lets the bridge (or any node
    daisy-chained off it) accept a wall-wart input directly instead of
    only bus V+ from another node.
    - D1, D2: MBRD10200 Schottky diodes (10 A / 200 V, DPAK, LCSC C260297)
    in series between each DC jack and the corresponding JBUS V+. Protects
2026-04-14 hardware: vendor TS-1187A tact switch footprint + approximate 3D model
    KiCad's stock Button_Switch_SMD:SW_Push_1P1T_XKB_TS-1187A footprint
    references a STEP file that is missing from the KiCad asset tree — the
    button renders as bare pads with no body.
    Vendor the footprint as tsumikoro:SW_Push_1P1T_XKB_TS-1187A and repoint
    the 3D model at a copy of the CK KMR2 STEP (close-enough tact switch
    body, 4.2x3.2 mm vs TS-1187A's 4.5x4.5 mm). Gets us a visible body in
2026-04-15 ministepper: finalize pin map + sync firmware to hardware rev 0.1
    Hardware (schematic + docs) and firmware now share a single source of
    truth for the STM32G071G8U6 UFQFPN-28 pinout:
    - USART2 on PA2/PA3 (RS-485) — dedicated pins, no SYSCFG remap needed
    (unlike the servo's STM32G030 where PA11/PA12 shared pads with
    PA9/PA10)
    - Two independent step timers: TIM1_CH1 on PA8 (STEP1) and TIM2_CH1
2026-04-15 ministepper: refactor as multi-channel design via reusable sub-sheet
    New hardware/ministepper/stepper_channel.kicad_sch contains a single
    TMC2130 stepper channel — one TMC2130-LA plus all the per-driver support
    passives from the datasheet:
    - RSA/RSB 0.1 ohm 1% 1210 sense (standard, populated)
    - RSA_M/RSB_M 0.68 ohm 1% 1210 sense (micro / 28BYJ-48 variant, DNP)
    - C_VS_BULK 10 uF 50V 1210 motor-rail bulk
2026-04-15 ministepper: fix sheet-pin text justify (labels were overlapping pin stubs)
    On left-edge sheet pins (angle=180) I had justify=right, which made the
    label text flow LEFT from the pin origin — colliding with the pin arrow
    stub that also extends left. Symmetric mistake on right-edge pins
    (angle=0 + justify=left flowing outward).
    Flipped on all 24 pins across both stepper sheet instances:
    angle 180 (left edge) -> justify left (text flows right INTO sheet)
2026-04-20 deps(deps): bump esphome
    Bumps the esphome group in /firmware/tsumikoro-bridge with 1 update: [esphome](https://github.com/esphome/esphome).
    Updates `esphome` from 2026.3.3 to 2026.4.1
    - [Release notes](https://github.com/esphome/esphome/releases)
    - [Commits](https://github.com/esphome/esphome/compare/2026.3.3...2026.4.1)
    ---
    updated-dependencies:
2026-04-27 deps(deps): bump firmware/common/STM32CubeG0 from `a019f83` to `878a6fd` (#48)
    Bumps [firmware/common/STM32CubeG0](https://github.com/STMicroelectronics/STM32CubeG0) from `a019f83` to `878a6fd`.
    - [Commits](https://github.com/STMicroelectronics/STM32CubeG0/compare/a019f83e7693348cf50f1466756ea985d3a96163...878a6fd8ad440c70ee32bc6d7ad526babb6e04f4)
    ---
    updated-dependencies:
    - dependency-name: firmware/common/STM32CubeG0
    dependency-version: 878a6fd8ad440c70ee32bc6d7ad526babb6e04f4
2026-05-11 deps(deps): bump esphome (#50)
    Bumps the esphome group in /firmware/tsumikoro-bridge with 1 update: [esphome](https://github.com/esphome/esphome).
    Updates `esphome` from 2026.4.1 to 2026.4.5
    - [Release notes](https://github.com/esphome/esphome/releases)
    - [Commits](https://github.com/esphome/esphome/compare/2026.4.1...2026.4.5)
    ---
    updated-dependencies:
2026-06-08 deps(deps): bump esphome
    Bumps the esphome group in /firmware/tsumikoro-bridge with 1 update: [esphome](https://github.com/esphome/esphome).
    Updates `esphome` from 2026.5.1 to 2026.5.3
    - [Release notes](https://github.com/esphome/esphome/releases)
    - [Commits](https://github.com/esphome/esphome/compare/2026.5.1...2026.5.3)
    ---
    updated-dependencies:

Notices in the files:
firmware/tsumikoro-servo/src/servo_pwm.c:
Copyright (c) 2025 Yann Ramin
SPDX-License-Identifier: Apache-2.0
hardware/servo/servo.kicad_pcb:
© 2026 StackFoundry LLC
